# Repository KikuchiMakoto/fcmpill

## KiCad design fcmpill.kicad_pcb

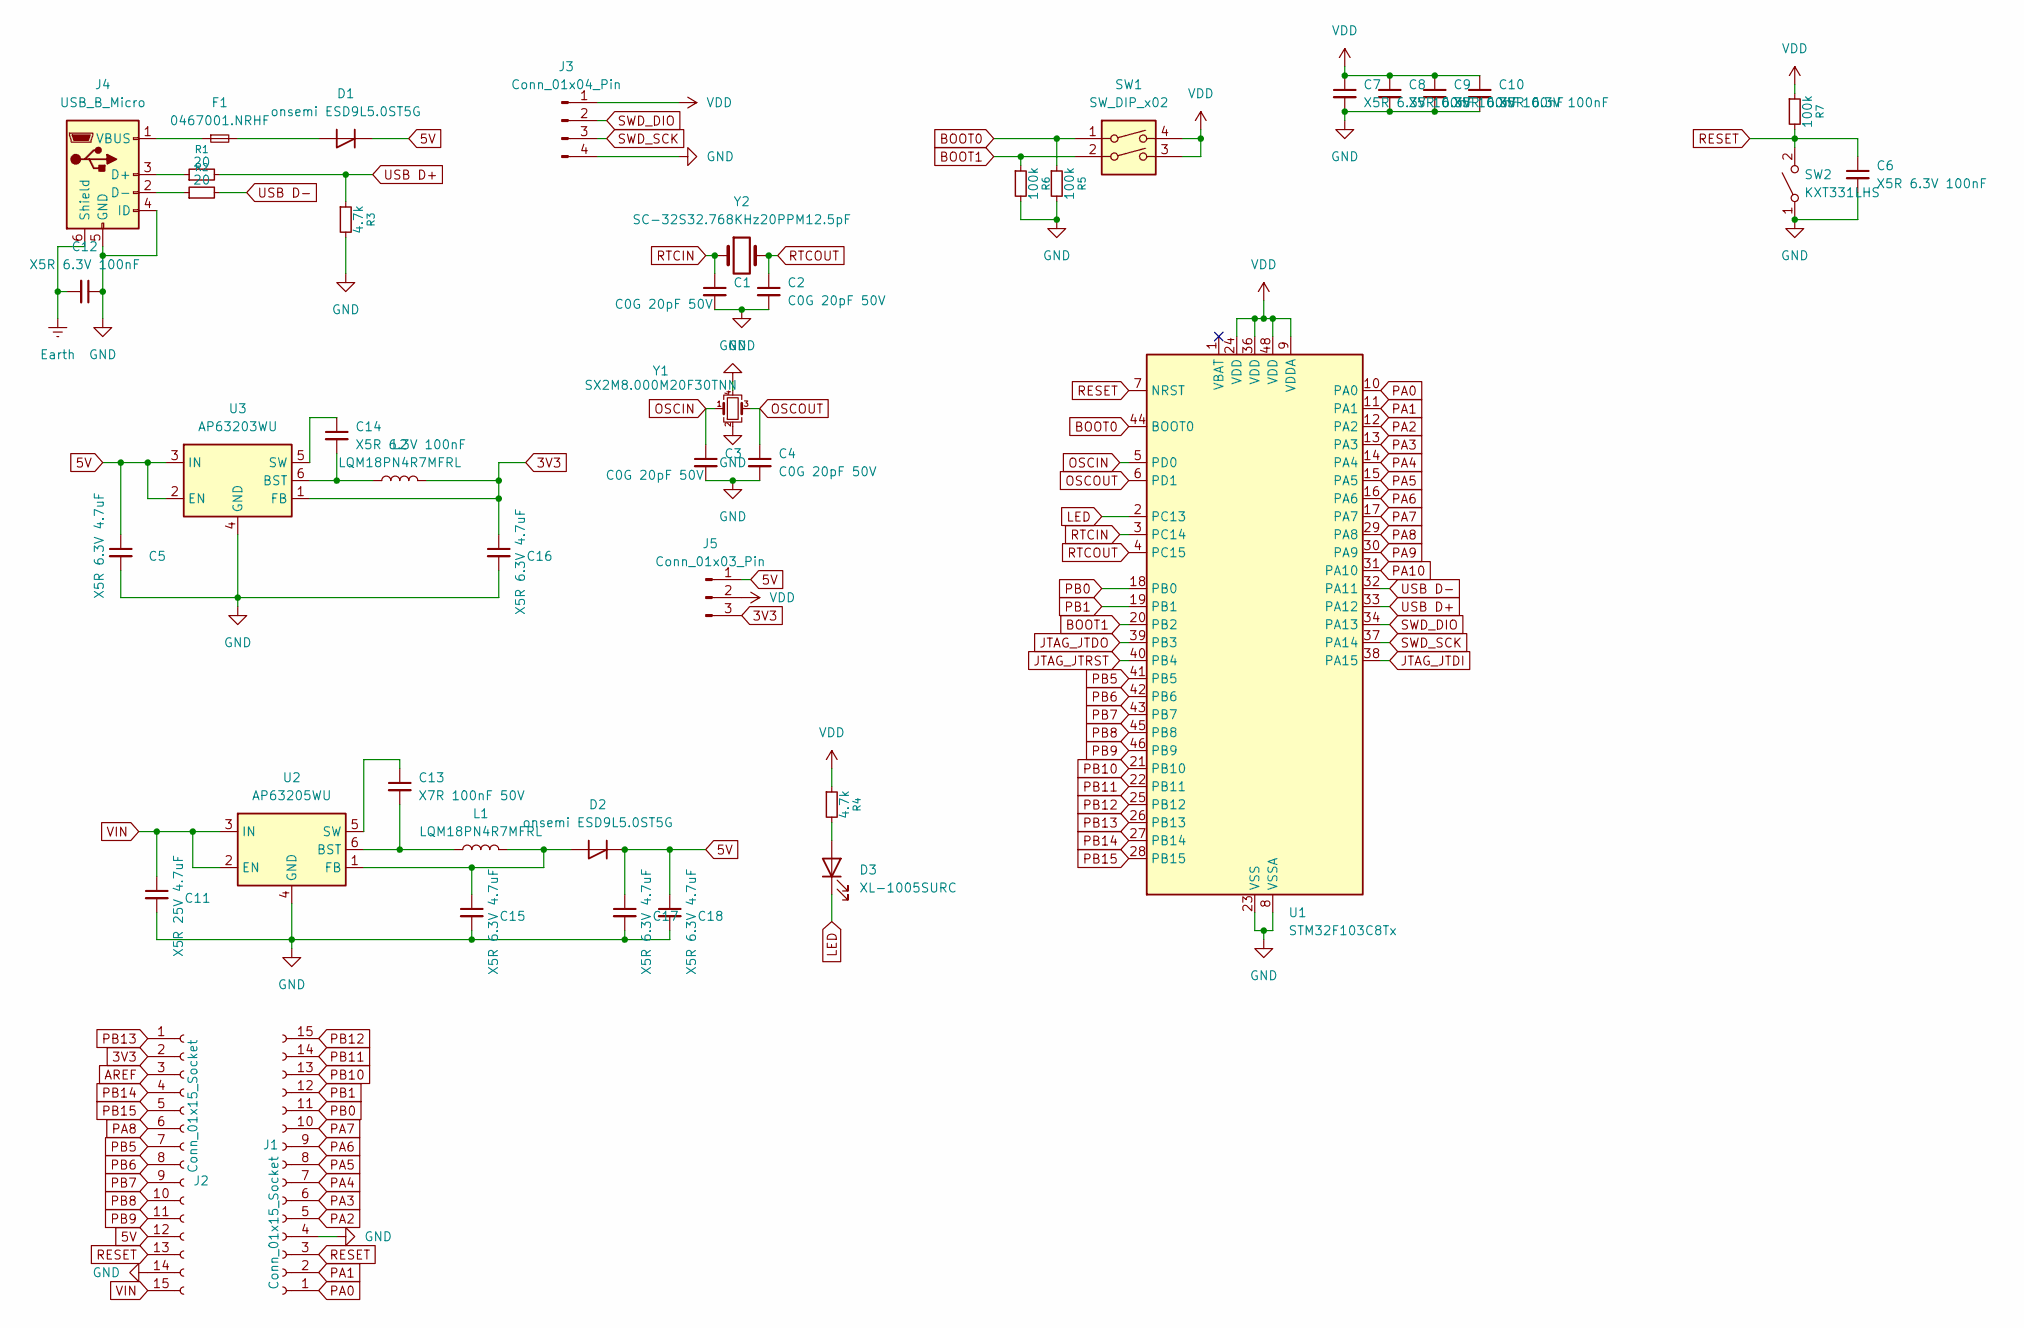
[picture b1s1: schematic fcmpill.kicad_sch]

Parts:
C1, C2, C3, C4: C0G 20pF 50V; C_0402_1005Metric
C5, C15, C16, C17, C18: X5R 6.3V 4.7uF; C_0402_1005Metric
C6, C7, C8, C9, C10, C14: X5R 6.3V 100nF; C_0402_1005Metric
C11: X5R 25V 4.7uF; C_0603_1608Metric
C12: X5R 6.3V 100nF; C_0603_1608Metric
C13: X7R 100nF 50V; C_0402_1005Metric
D1, D2: onsemi ESD9L5.0ST5G; D_SOD-923
D3: XL-1005SURC; LED_0402_1005Metric
F1: 0467001.NRHF; Fuse_0603_1608Metric
J1, J2: Conn_01x15_Socket; PinHeader_1x15_P2.54mm_Vertical
J3: Conn_01x04_Pin; JST_PH_S4B-PH-K_1x04_P2.00mm_Horizontal
J4: USB_B_Micro; USB_Micro-B_Amphenol_10118193-0001LF_Horizontal
J5: Conn_01x03_Pin; Voltage_Selector
L1, L2: LQM18PN4R7MFRL; L_0603_1608Metric
R1, R2: 20; R_0603_1608Metric
R3: 4.7k; R_0603_1608Metric
R4: 4.7k; R_0402_1005Metric
R5, R6, R7: 100k; R_0402_1005Metric
SW1: SW_DIP_x02; SW_DIP_SPSTx02_Slide_KingTek_DSHP02TS_W7.62mm_P1.27mm
SW2: KXT331LHS; SW_SPST_CK_KXT3
U1: STM32F103C8Tx; LQFP-48_7x7mm_P0.5mm
U2: AP63205WU; TSOT-23-6
U3: AP63203WU; TSOT-23-6
Y1: SX2M8.000M20F30TNN; Crystal_SMD_2520-4Pin_2.5x2.0mm
Y2: SC-32S32.768KHz20PPM12.5pF; Crystal_SMD_3215-2Pin_3.2x1.5mm

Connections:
3V3: C16.1, J2.2, J5.3, L2.2, U3.1 (FB)
5V: C5.1, C17.1, C18.1, D1.1 (K), D2.1 (K), J2.12, J5.1, U3.2 (EN), U3.3 (IN)
AREF: J2.3
BOOT0: R5.1, SW1.1, U1.44 (BOOT0)
BOOT1: R6.1, SW1.2, U1.20 (PB2)
Earth: C12.2, J4.6 (Shield)
GND: C1.2, C2.2, C3.2, C4.2, C5.2, C6.2, C7.2, C8.2, C9.2, C10.2, C11.2, C12.1, C15.2, C16.2, C17.2, C18.2, J1.4, J2.14, J3.4, J4.4 (ID), J4.5 (GND), R3.2, R5.2, R6.2, SW2.1 (A), U1.8 (VSSA), U1.23 (VSS), U1.35 (VSS), U1.47 (VSS), U2.4 (GND), U3.4 (GND), Y1.2, Y1.4
JTAG_JTDI: U1.38 (PA15)
JTAG_JTDO: U1.39 (PB3)
JTAG_JTRST: U1.40 (PB4)
LED: D3.1 (K), U1.2 (PC13)
unnamed: D1.2 (A), F1.2
unnamed: C15.1, D2.2 (A), L1.2, U2.1 (FB)
unnamed: D3.2 (A), R4.2
unnamed: J4.3 (D+), R1.1
unnamed: J4.2 (D-), R2.1
unnamed: F1.1, J4.1 (VBUS)
unnamed: C13.2, L1.1, U2.6 (BST)
unnamed: C13.1, U2.5 (SW)
unnamed: C14.2, L2.1, U3.6 (BST)
unnamed: C14.1, U3.5 (SW)
OSCIN: C3.1, U1.5 (PD0), Y1.1
OSCOUT: C4.1, U1.6 (PD1), Y1.3
PA0: J1.1, U1.10 (PA0)
PA1: J1.2, U1.11 (PA1)
PA2: J1.5, U1.12 (PA2)
PA3: J1.6, U1.13 (PA3)
PA4: J1.7, U1.14 (PA4)
PA5: J1.8, U1.15 (PA5)
PA6: J1.9, U1.16 (PA6)
PA7: J1.10, U1.17 (PA7)
PA8: J2.6, U1.29 (PA8)
PA9: U1.30 (PA9)
PA10: U1.31 (PA10)
PB0: J1.11, U1.18 (PB0)
PB1: J1.12, U1.19 (PB1)
PB5: J2.7, U1.41 (PB5)
PB6: J2.8, U1.42 (PB6)
PB7: J2.9, U1.43 (PB7)
PB8: J2.10, U1.45 (PB8)
PB9: J2.11, U1.46 (PB9)
PB10: J1.13, U1.21 (PB10)
PB11: J1.14, U1.22 (PB11)
PB12: J1.15, U1.25 (PB12)
PB13: J2.1, U1.26 (PB13)
PB14: J2.4, U1.27 (PB14)
PB15: J2.5, U1.28 (PB15)
RESET: C6.1, J1.3, J2.13, R7.2, SW2.2 (B), U1.7 (NRST)
RTCIN: C1.1, U1.3 (PC14), Y2.1
RTCOUT: C2.1, U1.4 (PC15), Y2.2
SWD_DIO: J3.2, U1.34 (PA13)
SWD_SCK: J3.3, U1.37 (PA14)
USB D+: R1.2, R3.1, U1.33 (PA12)
USB D-: R2.2, U1.32 (PA11)
VDD: C7.1, C8.1, C9.1, C10.1, J3.1, J5.2, R4.1, R7.1, SW1.3, SW1.4, U1.9 (VDDA), U1.24 (VDD), U1.36 (VDD), U1.48 (VDD)
VIN: C11.1, J2.15, U2.2 (EN), U2.3 (IN)

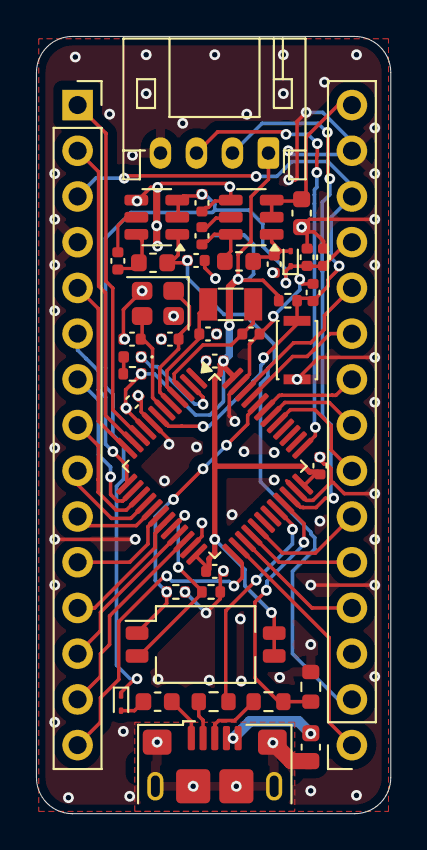
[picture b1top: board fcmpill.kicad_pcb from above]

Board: 2 copper layers, 19.7 x 43.2 mm, 43 parts (1 on the bottom side), 50 nets.

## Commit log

2025-09-13 2025/09/13 fabrication version
2025-09-15 20250915
2025-09-15 add thumbnail
